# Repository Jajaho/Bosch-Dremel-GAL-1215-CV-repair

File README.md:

# Dremel-PCB1857V1

Reverse engineering of a Dremel 12v battery charger.
The pcb has the markings: PCB1857V1
This repository contains KiCad schematics of the main side of its power supply.
Some component values have been measured and added.

See in the [kicad](https://github.com/Jajaho/Dremel-PCB1857V1/tree/master/kicad) directory for the schematic source file or get a printed pdf from the [actions](https://github.com/Jajaho/Dremel-PCB1857V1/actions) tab.

## Battery

It is an open secret that Bosch and Dremel (Dremel being a division in the Robert Bosch Tool Corporation since 1993) batteries are compatible except for the bottom plastic shell with the retainment clips. If I had to take a wild guess I would say they are probably even manufactured in the same factory.

Even though the battery exposes two contacts for balance charging labeled C1 and C2 only C1 is connected to the charger. 

The kicker however is that inside the Bosch GSR BAT411 the both C1 and C2 are not actually connected to the batteries, as you can clearly see in the picture below:

Source: [BOSCH Upgrade Battery / Change Old Dead Li Ion Cell / GSR BAT411 - CMC DIY (youtube)](https://www.youtube.com/watch?v=-DkphFzir5k)

From what I could gather from some pictures online the internal connections look like this:

### Why is this a problem?  

The connections to the individual battery cells are required for balance charging.
Due to manufacturing variations the internal resistance $R_1$, $R_2$ of two cells can vary. When the battery is discharged a current $I$ is flowing through all cells equally due to Kirchhoff's current law. This causes the voltages of the individual cells to decrease according to  

$$
\begin{align*}
    U_1 = R_1 \cdot I  \\
    U_2 = R_2 \cdot I
\end{align*}
$$

Resulting in a voltage difference of  

$$
\begin{align*}
    \Delta U = U_1 - U_2 
\end{align*}
$$

When the battery gets charged again this difference would get annihilated if the resistances were constant, but they are not. Over many discharge/charging cycles $\Delta U$ can grow to be substantial difference which could cause the battery to fail because:  
a) One cell get under discharged, or  
b) the other cell gets overcharged.

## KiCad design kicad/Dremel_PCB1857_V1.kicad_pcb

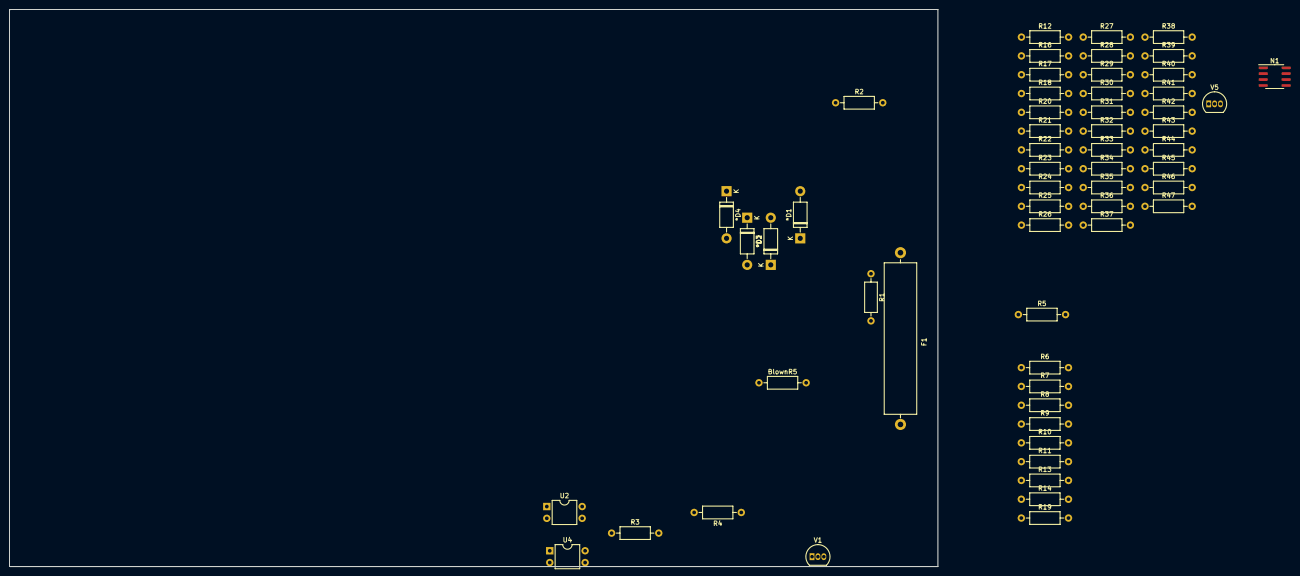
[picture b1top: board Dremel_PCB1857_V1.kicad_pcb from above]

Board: 2 copper layers, 200.0 x 120.0 mm, 57 parts (0 on the bottom side), 31 nets, no tracks yet.

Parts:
*D1, *D2, *D3, *D4: 1N4007; D_DO-41_SOD81_P10.16mm_Horizontal
BlownR5: R; R_Axial_DIN0207_L6.3mm_D2.5mm_P10.16mm_Horizontal
F1: 1.25A; Fuse_SunFuse-6HP
N1: TL1431A; SOIC-8_3.9x4.9mm_P1.27mm
R1: Thermistor_PTC; R_Axial_DIN0207_L6.3mm_D2.5mm_P10.16mm_Horizontal
R2: 680k; R_Axial_DIN0207_L6.3mm_D2.5mm_P10.16mm_Horizontal
R3, R12, R16, R17, R18, R22, R25, R26, R29, R31, R32, R34, R37, R42, R43, R44, R45, R46, R47: R; R_Axial_DIN0207_L6.3mm_D2.5mm_P10.16mm_Horizontal
R4, R5: 510k; R_Axial_DIN0207_L6.3mm_D2.5mm_P10.16mm_Horizontal
R6: 30R; R_Axial_DIN0207_L6.3mm_D2.5mm_P10.16mm_Horizontal
R7: 160R; R_Axial_DIN0207_L6.3mm_D2.5mm_P10.16mm_Horizontal
R8: 2.6k; R_Axial_DIN0207_L6.3mm_D2.5mm_P10.16mm_Horizontal
R9, R30: 1k; R_Axial_DIN0207_L6.3mm_D2.5mm_P10.16mm_Horizontal
R10: 4.7R; R_Axial_DIN0207_L6.3mm_D2.5mm_P10.16mm_Horizontal
R11: 47k; R_Axial_DIN0207_L6.3mm_D2.5mm_P10.16mm_Horizontal
R13: 100R; R_Axial_DIN0207_L6.3mm_D2.5mm_P10.16mm_Horizontal
R14, R19: 300k; R_Axial_DIN0207_L6.3mm_D2.5mm_P10.16mm_Horizontal
R20: 0.22 R; R_Axial_DIN0207_L6.3mm_D2.5mm_P10.16mm_Horizontal
R21: O.22 R; R_Axial_DIN0207_L6.3mm_D2.5mm_P10.16mm_Horizontal
R23, R27, R35, R39: 10k; R_Axial_DIN0207_L6.3mm_D2.5mm_P10.16mm_Horizontal
R24: 29.4k; R_Axial_DIN0207_L6.3mm_D2.5mm_P10.16mm_Horizontal
R28: 2k; R_Axial_DIN0207_L6.3mm_D2.5mm_P10.16mm_Horizontal
R33: 20k; R_Axial_DIN0207_L6.3mm_D2.5mm_P10.16mm_Horizontal
R36: 6.04k; R_Axial_DIN0207_L6.3mm_D2.5mm_P10.16mm_Horizontal
R38: 12k; R_Axial_DIN0207_L6.3mm_D2.5mm_P10.16mm_Horizontal
R40: 360R; R_Axial_DIN0207_L6.3mm_D2.5mm_P10.16mm_Horizontal
R41: 25.5k; R_Axial_DIN0207_L6.3mm_D2.5mm_P10.16mm_Horizontal
U2, U4: B179; DIP-4_W7.62mm
V1: 2N3904; TO-92_Inline
V5: BC546A; TO-92_Inline

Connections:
/Battery/C1: R42.2, R44.1
/Battery/NTC: R45.1, R46.1
/Secondary side/L4_6: R18.2, R20.2, R21.2, R25.2, R30.2
/Secondary side/Pin 1: R23.1, R26.1, R34.2, R44.2, R45.2, V5.3 (E)
/Secondary side/Pin 9: R39.1, R40.1
/Secondary side/Pin 10: R33.1, R36.2, R38.2, R41.2
/Secondary side/V2: R17.2, R28.2, V5.1 (C)
GND2: N1.2 (A), N1.3 (A), N1.6 (A), N1.7 (A), R20.1, R21.1, R29.2, R31.1, U4.2
unnamed: R12.1, R17.1
unnamed: R16.2, R18.1, R22.2, R33.2
unnamed: *D1.2 (A), *D3.1 (K)
unnamed: *D1.1 (K), *D2.1 (K), R4.1
unnamed: *D2.2 (A), *D4.1 (K)
unnamed: *D3.2 (A), *D4.2 (A), BlownR5.2, R9.1, V1.1 (E)
unnamed: R1.1, R2.1
unnamed: F1.2, R2.2
unnamed: R13.2, R14.1, R19.1
unnamed: N1.1 (K), R28.1, V5.2 (B)
unnamed: N1.8 (REF), R31.2, R34.1, R37.2
unnamed: R3.2, R8.1, R9.2, R10.1, V1.2 (B)
unnamed: R3.1, U2.3
unnamed: R4.2, R5.1
unnamed: R32.2, U4.1
unnamed: R35.1, R39.2
unnamed: R37.1, R47.2
unnamed: R24.2, R25.1, R26.2, R27.1
unnamed: R30.1, R35.2
unnamed: R6.2, V1.3 (C)
unnamed: R14.2, R19.2
unnamed: R5.2, R6.1, R7.1, R8.2, R11.1
unnamed: BlownR5.1, R11.2

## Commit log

2023-07-06 Add old project files
2023-07-06 Removed kicad backup files
2023-07-25 Remove TP-E15 kicad project file
2023-07-25 Add Tested parameter to schematics
2023-07-25 Remove auto saved files
2023-07-26 Added secondary side to schematic
2023-07-26 Add R30
2023-08-03 Resolve R20 duplicate
    Update README with attempt 2
2023-08-03 Update README.md/R20 in xcf
2023-08-04 Tidy up main side layout
2023-08-04 Add R10 and V11 connection
2023-08-04 Add #auto_saved_files# to gitignore
2023-08-04 Add battery pictures
2023-08-04 Rotate picture
2023-08-04 Split schematic into mutliple hierachical sheets
2023-08-04 Move troubleshooting to seperate md file
2023-08-04 Update README.md and battery schematic
2023-08-05 Add kibot action with quickstart config
2023-08-05 Update KiBot action tag to match KiCad7
2023-08-05 Update Kibot action name
2023-08-05 Update READMEs and remove datasheet
2023-08-05 Add footprints
2023-08-05 Fix symbol names
2023-08-05 Label NOTR12 and NOTR43
2023-08-05 Add kibot.yaml config file
2023-08-05 Update to API 2 / Set path
2023-08-05 Update action tags
2023-08-05 Fix kibot version
2023-08-05 Add kibot.yaml hook
2023-08-05 Deactivate erc and drc
2023-08-06 Removed variants
2023-08-06 Fix upload path
2023-08-06 Update schematic
2023-08-08 Resolve R12 and R45 conflict
2023-08-09 Add attempt 3
2023-08-24 Repair resonant circuitry
2023-08-24 Add images to troubleshooting.md
2023-08-24 Plugged in battery -> firework
2023-08-24 Add article.md
2023-09-12 Add R5 value
2023-09-14 Measurements of working Bosch pcb
2023-09-22 Adds dremel battery schematic
2023-09-22 Create artifacts manuals
2023-09-22 Update article
2023-09-23 Moved article to jajaho.github.io
2023-11-08 Repaired
2023-11-08 Im done
